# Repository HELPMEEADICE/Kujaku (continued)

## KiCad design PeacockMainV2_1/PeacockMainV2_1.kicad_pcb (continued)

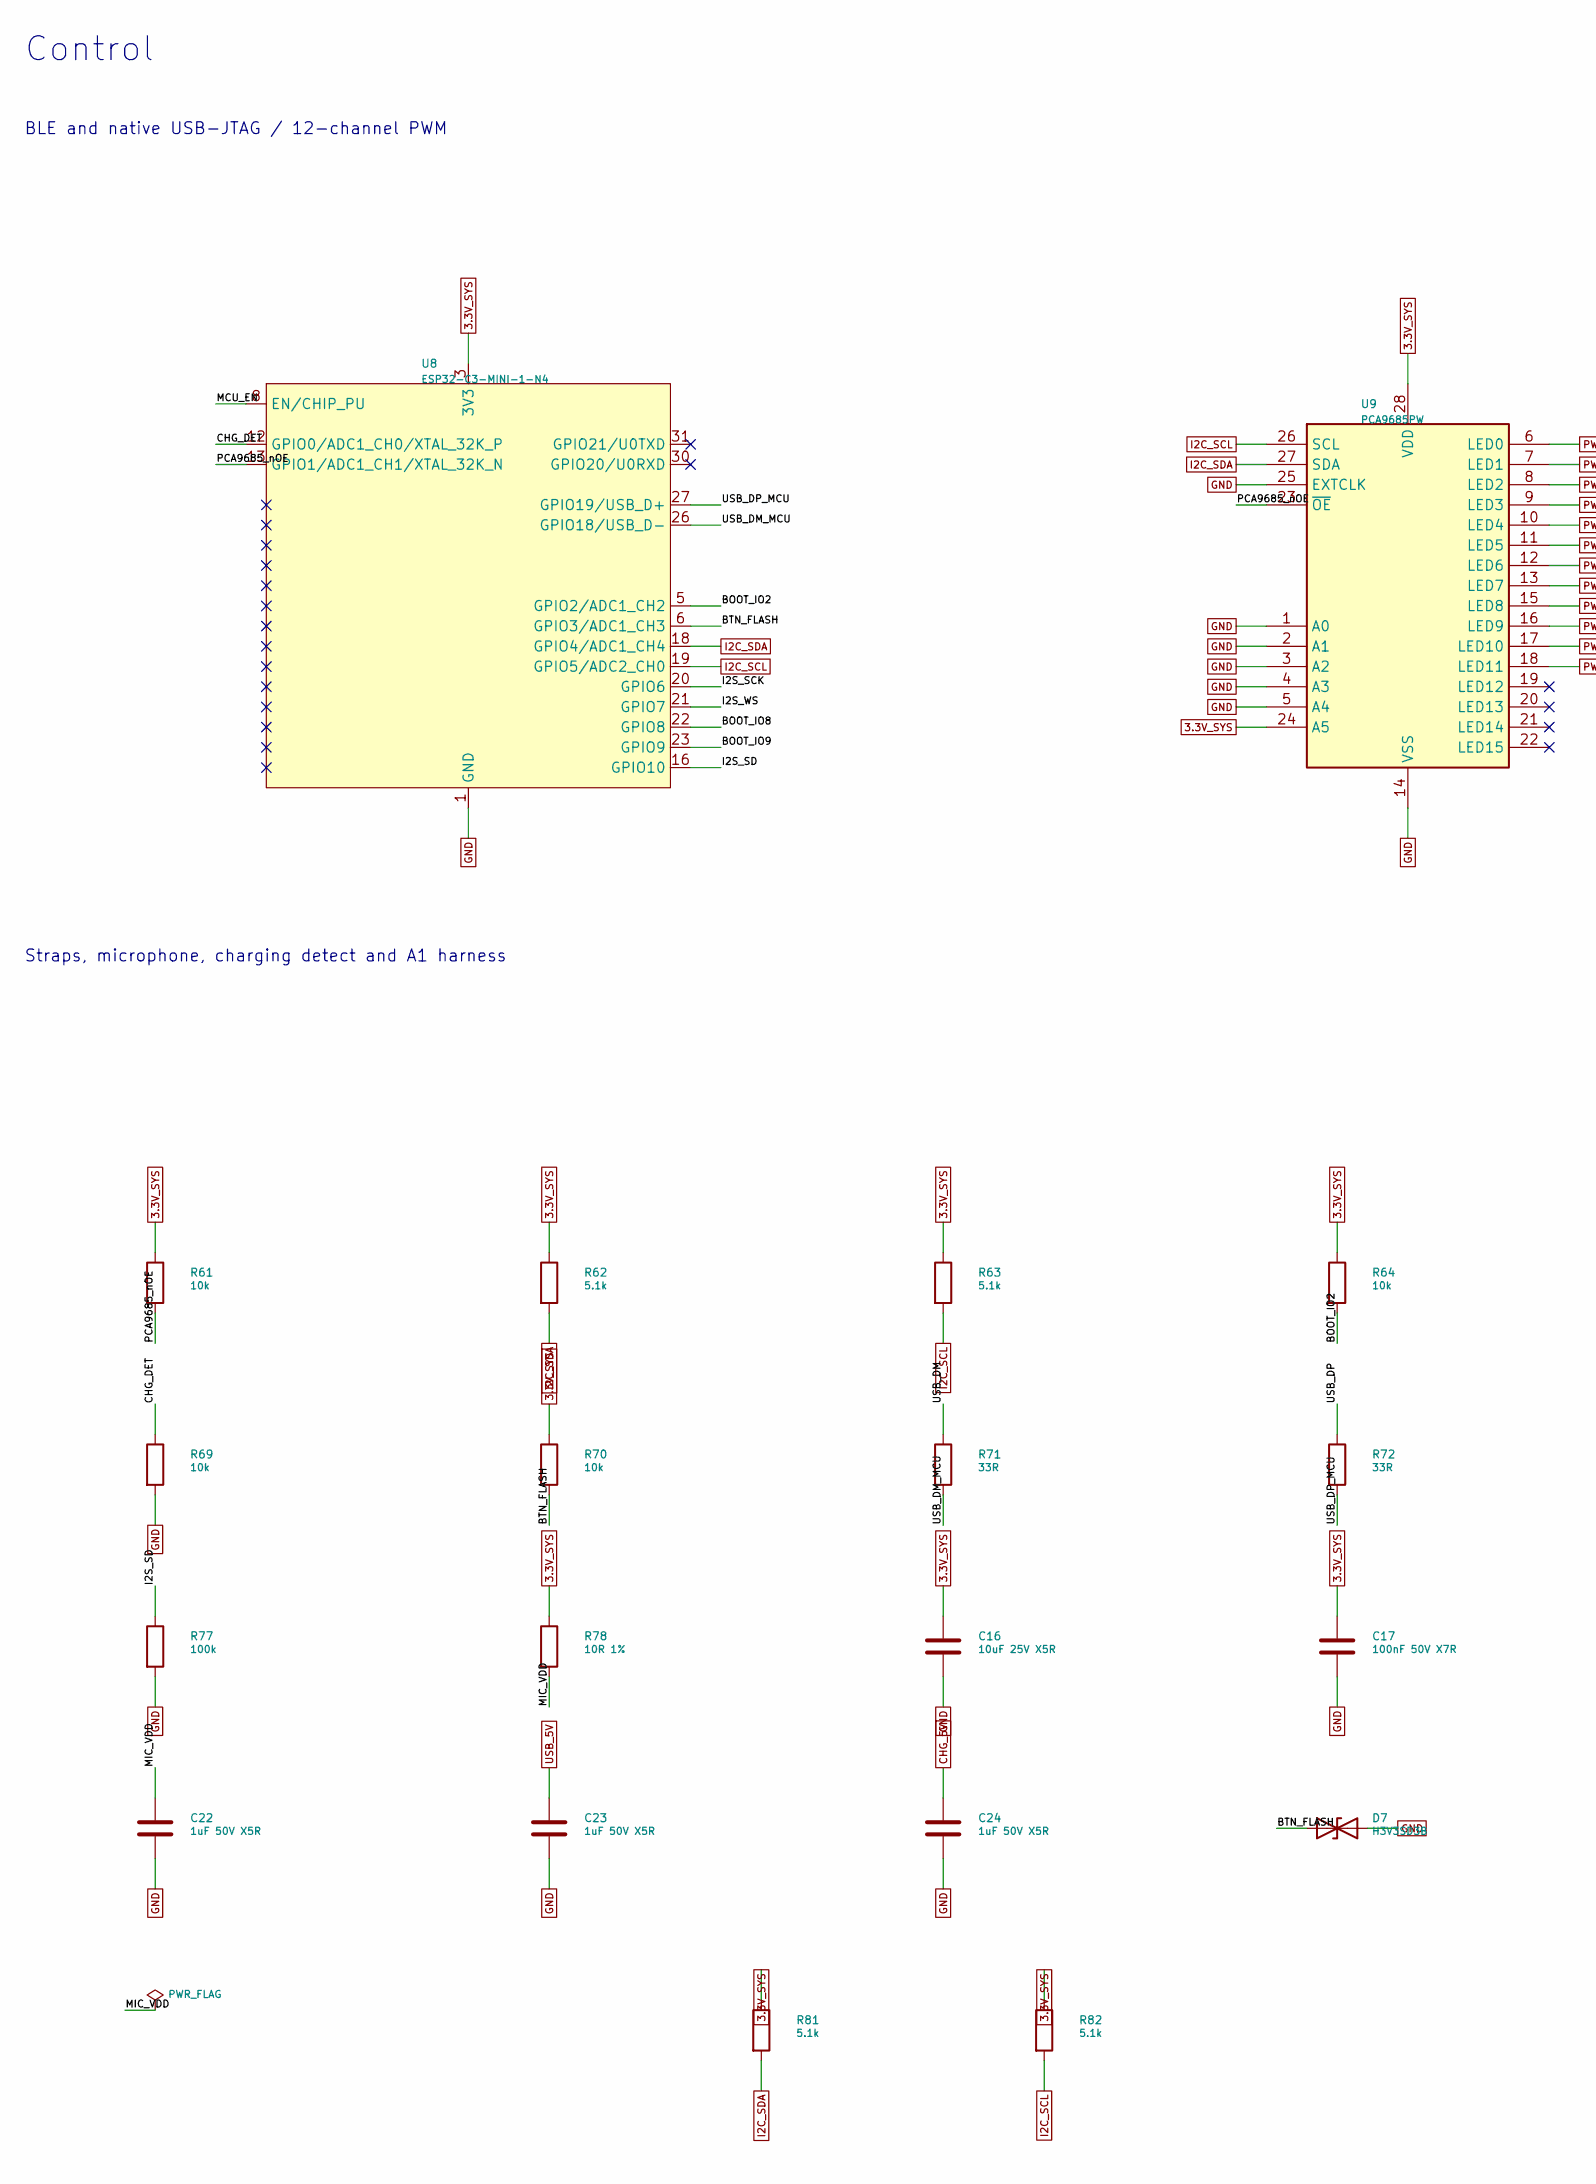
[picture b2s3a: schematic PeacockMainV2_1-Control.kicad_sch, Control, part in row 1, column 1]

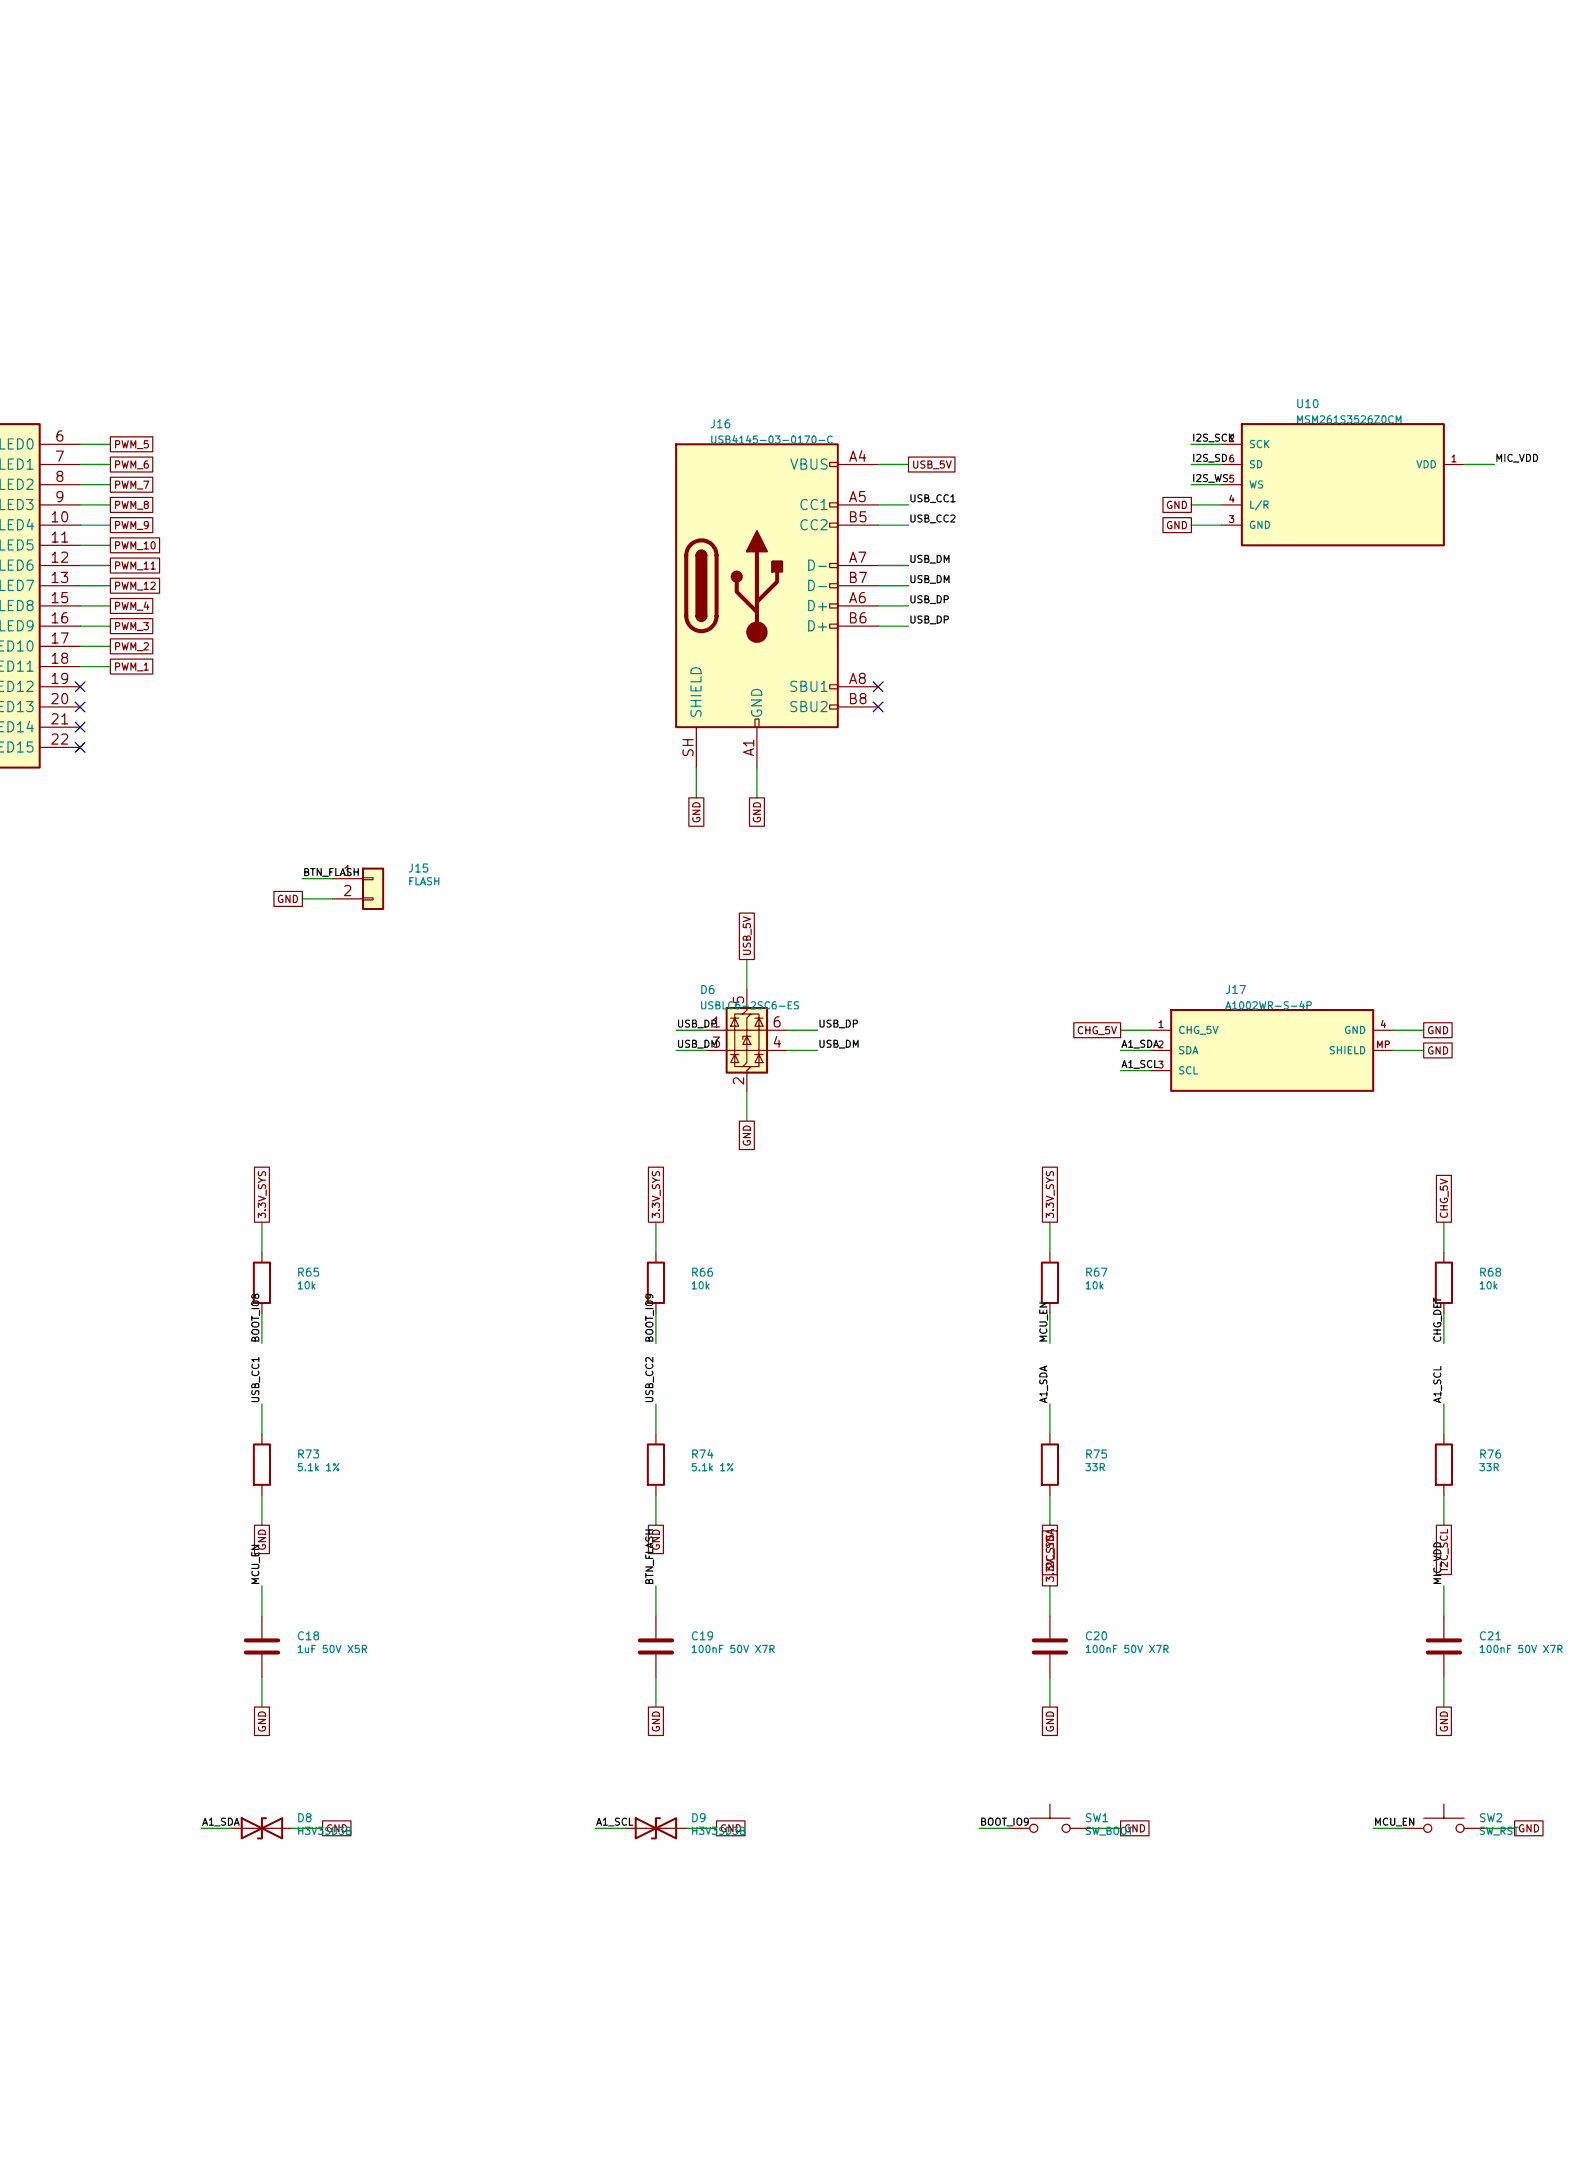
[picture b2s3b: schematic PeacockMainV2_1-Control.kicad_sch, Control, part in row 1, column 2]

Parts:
C16: 10uF 25V X5R; C_0805_2012Metric; MPN CL21A106KAYNNNE; LCSC C15850
C17, C21: 100nF 50V X7R; C_0402_1005Metric; MPN CL05B104KB54PNC; LCSC C307331
C18, C22, C23, C24: 1uF 50V X5R; C_0603_1608Metric; MPN CL10A105KB8NNNC; LCSC C15849
C19, C20: 100nF 50V X7R; C_0603_1608Metric; MPN CC0603KRX7R9BB104; LCSC C14663
D6: USBLC6-2SC6-ES; SOT-23-6; MPN USBLC6-2SC6-ES; LCSC C5180249
D7, D8, D9: H3V3SD3B; D_SOD-323; MPN H3V3SD3B; LCSC C20615802
J15: FLASH; Remote_Switch
J16: USB4145-03-0170-C; USB_C_Receptacle_GCT_USB4145-03-0170-C_Vertical; MPN USB4145-03-0170-C; LCSC C5181332
J17: A1002WR-S-4P; JST_SH_SM04B-SRSS-TB_1x04-1MP_P1.00mm_Horizontal; MPN A1002WR-S-4P; LCSC C239522
R61, R64, R65, R66, R67, R68, R69, R70: 10k; R_0603_1608Metric; MPN 0603WAF1002T5E; LCSC C25804
R62, R63, R81, R82: 5.1k; R_0603_1608Metric; MPN 0603WAF5101T5E; LCSC C23186
R71: 33R; R_0402_1005Metric; MPN 0402WGF330JTCE; LCSC C25105
R72, R75, R76: 33R; R_0603_1608Metric; MPN 0603WAF330JT5E; LCSC C23140
R73, R74: 5.1k 1%; R_0603_1608Metric; MPN 0603WAF5101T5E; LCSC C23186
R77: 100k; R_0603_1608Metric; MPN 0603WAF1003T5E; LCSC C25803
R78: 10R 1%; R_0603_1608Metric; MPN 0603WAF100JT5E; LCSC C22859
SW1: SW_BOOT; SW_SPST_TL3342; MPN TS5216A 160gf; LCSC C2681484
SW2: SW_RST; SW_SPST_TL3342; MPN TS5216A 160gf; LCSC C2681484
U8: ESP32-C3-MINI-1-N4; ESP32-C3-MINI-1; MPN ESP32-C3-MINI-1-N4; LCSC C2838502
U9: PCA9685PW; TSSOP-28_4.4x9.7mm_P0.65mm; MPN PCA9685PW,118; LCSC C2678753
U10: MSM261S3526Z0CM; MSM261S3526Z0CM_3.50x2.65; MPN MSM261S3526Z0CM; LCSC C966933

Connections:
3.3V_SYS: C16.1, C17.1, C20.1, R61.1, R62.1, R63.1, R64.1, R65.1, R66.1, R67.1, R70.1, R78.1, R81.1, R82.1, U8.3 (3V3), U9.24 (A5), U9.28 (VDD); also elsewhere on the board
/Control/A1_SCL: D9.1 (A1), J17.3 (SCL), R76.1
/Control/A1_SDA: D8.1 (A1), J17.2 (SDA), R75.1
/Control/BOOT_IO2: R64.2, U8.5 (GPIO2/ADC1_CH2)
/Control/BOOT_IO8: R65.2, U8.22 (GPIO8)
/Control/BOOT_IO9: R66.2, SW1.1, U8.23 (GPIO9)
/Control/BTN_FLASH: C19.1, D7.1 (A1), J15.1, R70.2, U8.6 (GPIO3/ADC1_CH3)
/Control/CHG_DET: R68.2, R69.1, U8.12 (GPIO0/ADC1_CH0/XTAL_32K_P)
/Control/I2S_SCK: U8.20 (GPIO6), U10.2 (SCK)
/Control/I2S_SD: R77.1, U8.16 (GPIO10), U10.6 (SD)
/Control/I2S_WS: U8.21 (GPIO7), U10.5 (WS)
/Control/MCU_EN: C18.1, R67.2, SW2.1, U8.8 (EN/CHIP_PU)
/Control/MIC_VDD: C21.1, C22.1, R78.2, U10.1 (VDD)
/Control/PCA9685_nOE: R61.2, U8.13 (GPIO1/ADC1_CH1/XTAL_32K_N), U9.23 (~OE)
/Control/USB_CC1: J16.A5 (CC1), R73.1
/Control/USB_CC2: J16.B5 (CC2), R74.1
/Control/USB_DM: D6.3 (I/O2), D6.4 (I/O2), J16.A7 (D-), J16.B7 (D-), R71.1
/Control/USB_DM_MCU: R71.2, U8.26 (GPIO18/USB_D-)
/Control/USB_DP: D6.1 (I/O1), D6.6 (I/O1), J16.A6 (D+), J16.B6 (D+), R72.1
/Control/USB_DP_MCU: R72.2, U8.27 (GPIO19/USB_D+)
CHG_5V: C24.1, J17.1 (CHG_5V), R68.1; also elsewhere on the board
GND: C16.2, C17.2, C18.2, C19.2, C20.2, C21.2, C22.2, C23.2, C24.2, D6.2 (GND), D7.2 (A2), D8.2 (A2), D9.2 (A2), J15.2, J16.A1 (GND), J16.A12 (GND), J16.B1 (GND), J16.B12 (GND), J16.SH (SHIELD), J17.4 (GND), J17.MP (SHIELD), R69.2, R73.2, R74.2, R77.2, SW1.2, SW2.2, U8.1 (GND), U8.2 (GND), U8.11 (GND), U8.14 (GND), U8.36 (GND), U8.37 (GND), U8.38 (GND), U8.39 (GND), U8.40 (GND), U8.41 (GND), U8.42 (GND), U8.43 (GND), U8.44 (GND), U8.45 (GND), U8.46 (GND), U8.47 (GND), U8.48 (GND), U8.49 (GND), U8.50 (GND), U8.51 (GND), U8.52 (GND), U8.53 (GND), U9.1 (A0), U9.2 (A1), U9.3 (A2), U9.4 (A3), U9.5 (A4), U9.14 (VSS), U9.25 (EXTCLK), U10.3 (GND), U10.4 (L/R); also elsewhere on the board
I2C_SCL: R63.2, R76.2, R82.2, U8.19 (GPIO5/ADC2_CH0), U9.26 (SCL); also elsewhere on the board
I2C_SDA: R62.2, R75.2, R81.2, U8.18 (GPIO4/ADC1_CH4), U9.27 (SDA); also elsewhere on the board
PWM_1: U9.18 (LED11); also elsewhere on the board
PWM_2: U9.17 (LED10); also elsewhere on the board
PWM_3: U9.16 (LED9); also elsewhere on the board
PWM_4: U9.15 (LED8); also elsewhere on the board
PWM_5: U9.6 (LED0); also elsewhere on the board
PWM_6: U9.7 (LED1); also elsewhere on the board
PWM_7: U9.8 (LED2); also elsewhere on the board
PWM_8: U9.9 (LED3); also elsewhere on the board
PWM_9: U9.10 (LED4); also elsewhere on the board
PWM_10: U9.11 (LED5); also elsewhere on the board
PWM_11: U9.12 (LED6); also elsewhere on the board
PWM_12: U9.13 (LED7); also elsewhere on the board
USB_5V: C23.1, D6.5 (VBUS), J16.A4 (VBUS), J16.A9 (VBUS), J16.B4 (VBUS), J16.B9 (VBUS); also elsewhere on the board

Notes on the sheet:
Control
BLE and native USB-JTAG / 12-channel PWM
Straps, microphone, charging detect and A1 harness

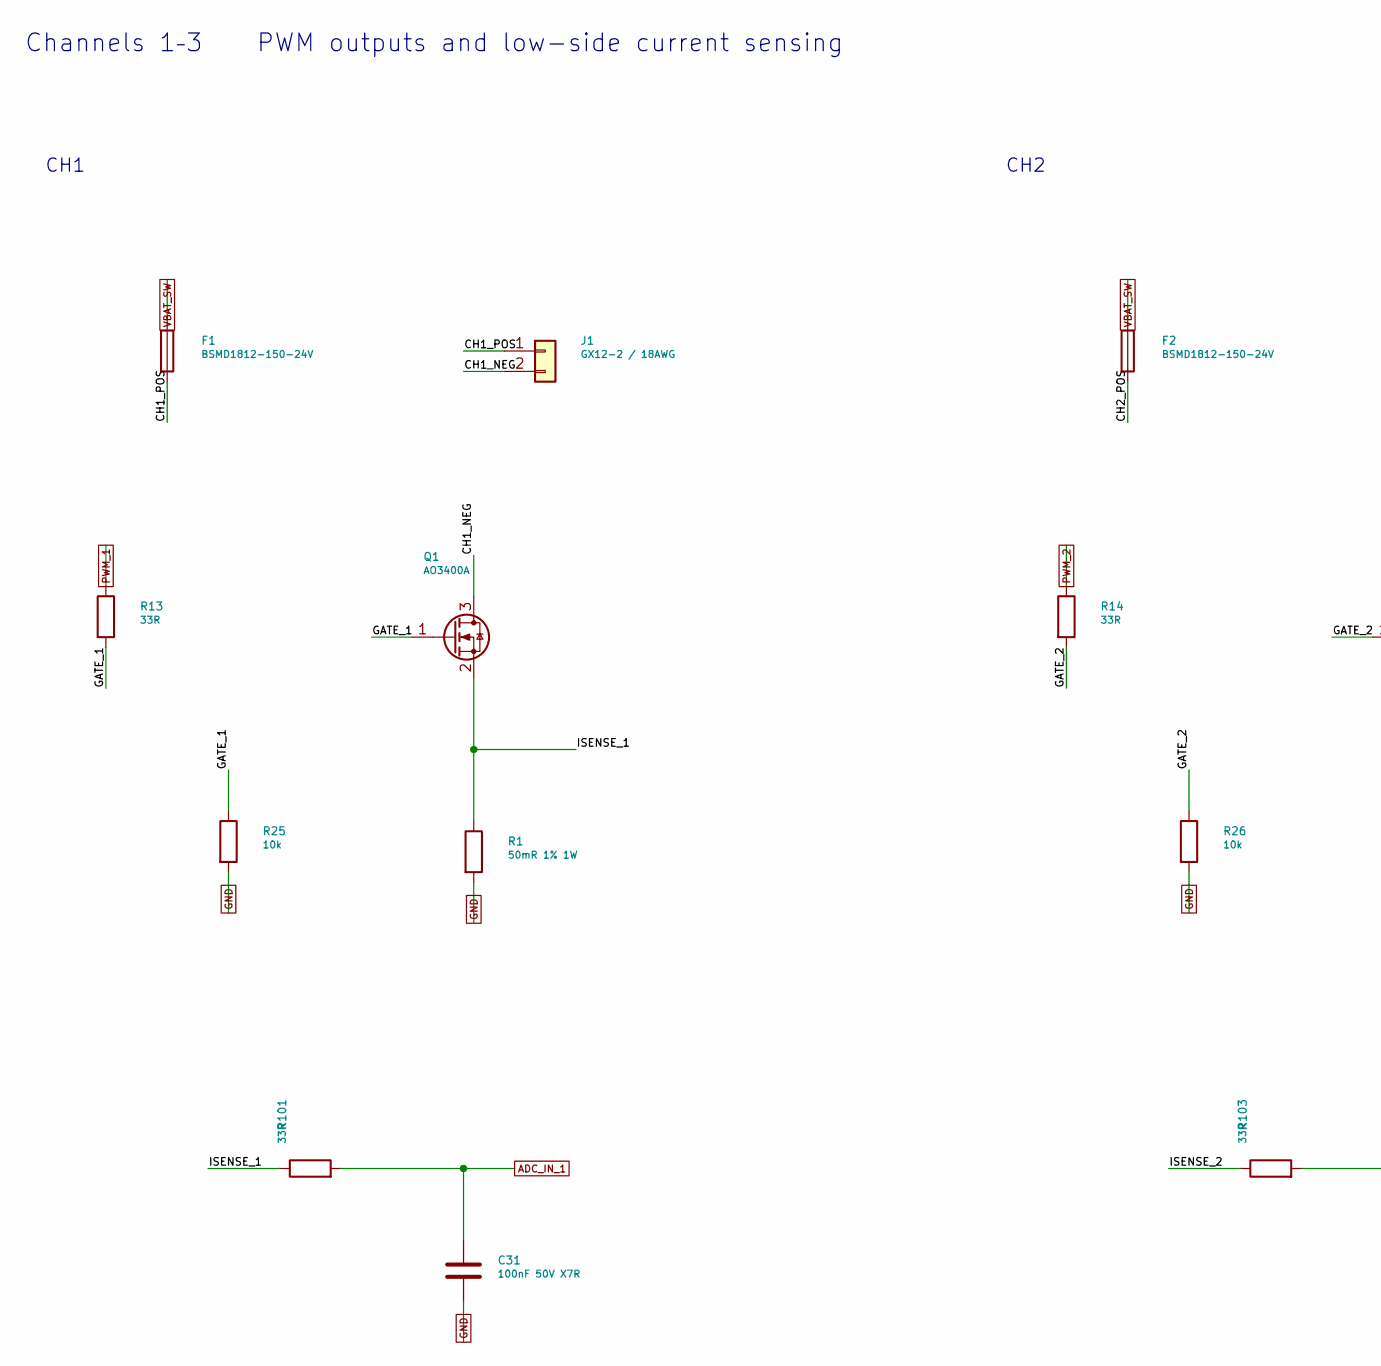
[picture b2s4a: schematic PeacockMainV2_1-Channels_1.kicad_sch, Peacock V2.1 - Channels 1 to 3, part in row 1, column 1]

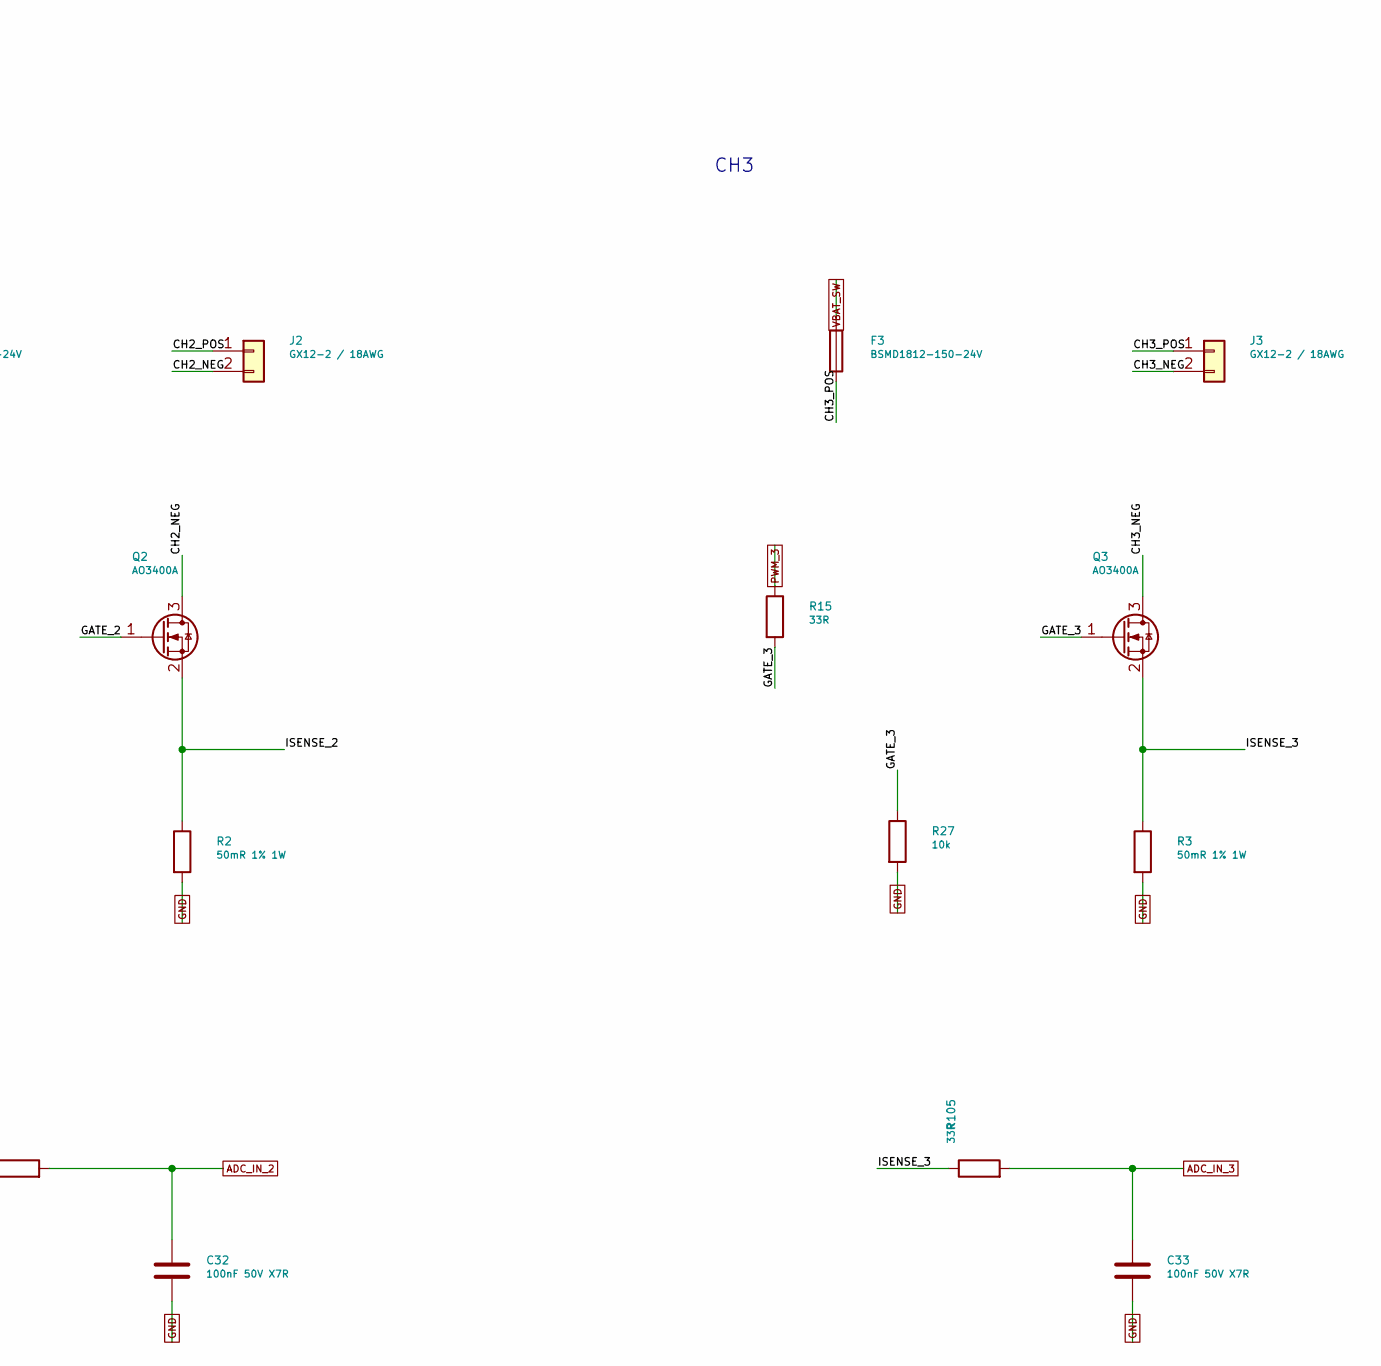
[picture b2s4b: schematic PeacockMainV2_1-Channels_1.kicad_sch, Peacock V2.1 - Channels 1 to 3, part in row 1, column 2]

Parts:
C31, C32, C33: 100nF 50V X7R; C_0603_1608Metric; MPN CC0603KRX7R9BB104; LCSC C14663
F1, F2, F3: BSMD1812-150-24V; R_1812_4532Metric; MPN BSMD1812-150-24V; LCSC C883153
J1, J2, J3: GX12-2 / 18AWG; GX12_Leadout_1x02_P5.00mm
Q1, Q2, Q3: AO3400A; SOT-23; MPN AO3400A; LCSC C20917
R1, R2, R3: 50mR 1% 1W; R_1206_3216Metric; MPN FRM121WFR050TM; LCSC C7467249
R13, R14, R15, R101, R103, R105: 33R; R_0603_1608Metric; MPN 0603WAF330JT5E; LCSC C23140
R25, R26, R27: 10k; R_0603_1608Metric; MPN 0603WAF1002T5E; LCSC C25804

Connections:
/Channels 1/CH1_NEG: J1.2, Q1.3 (D)
/Channels 1/CH1_POS: F1.2, J1.1
/Channels 1/CH2_NEG: J2.2, Q2.3 (D)
/Channels 1/CH2_POS: F2.2, J2.1
/Channels 1/CH3_NEG: J3.2, Q3.3 (D)
/Channels 1/CH3_POS: F3.2, J3.1
/Channels 1/GATE_1: Q1.1 (G), R13.2, R25.1
/Channels 1/GATE_2: Q2.1 (G), R14.2, R26.1
/Channels 1/GATE_3: Q3.1 (G), R15.2, R27.1
/Channels 1/ISENSE_1: Q1.2 (S), R1.1, R101.1
/Channels 1/ISENSE_2: Q2.2 (S), R2.1, R103.1
/Channels 1/ISENSE_3: Q3.2 (S), R3.1, R105.1
ADC_IN_1: C31.1, R101.2; also elsewhere on the board
ADC_IN_2: C32.1, R103.2; also elsewhere on the board
ADC_IN_3: C33.1, R105.2; also elsewhere on the board
GND: C31.2, C32.2, C33.2, R1.2, R2.2, R3.2, R25.2, R26.2, R27.2; also elsewhere on the board
PWM_1: R13.1; also elsewhere on the board
PWM_2: R14.1; also elsewhere on the board
PWM_3: R15.1; also elsewhere on the board
VBAT_SW: F1.1, F2.1, F3.1; also elsewhere on the board

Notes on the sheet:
Channels 1–3 PWM outputs and low-side current sensing
CH1
CH2
CH3

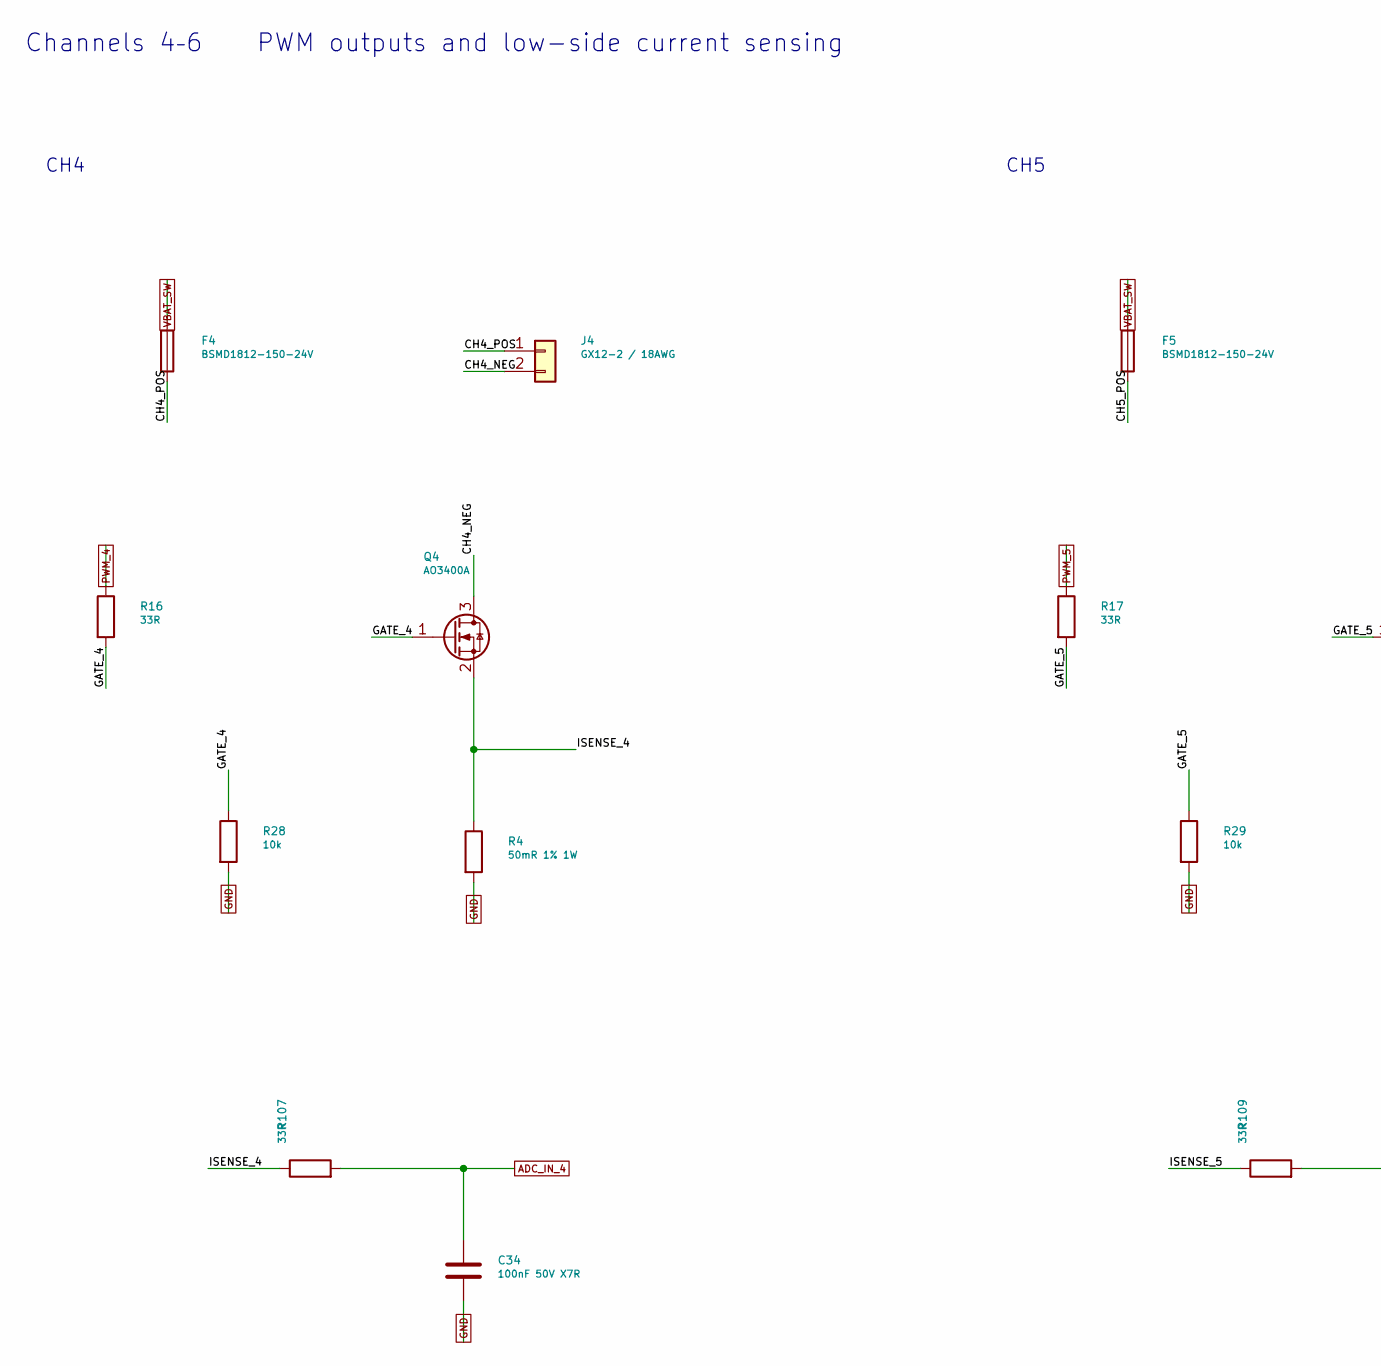
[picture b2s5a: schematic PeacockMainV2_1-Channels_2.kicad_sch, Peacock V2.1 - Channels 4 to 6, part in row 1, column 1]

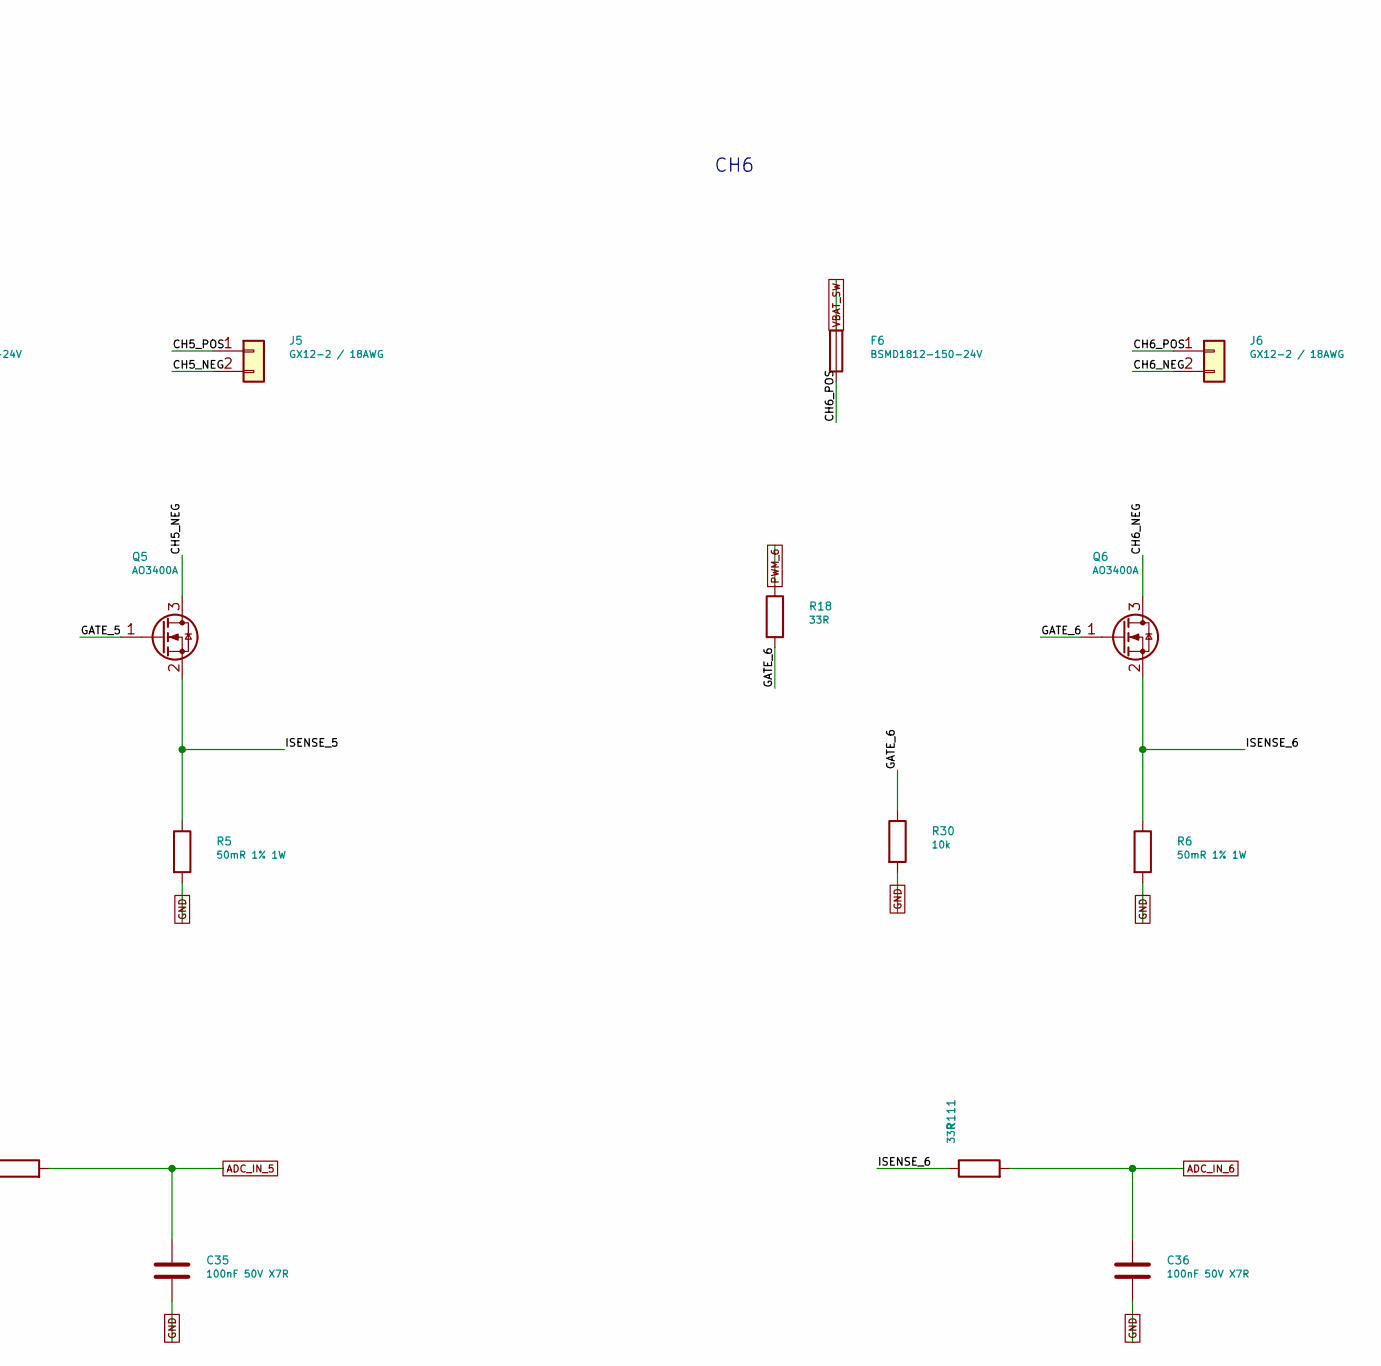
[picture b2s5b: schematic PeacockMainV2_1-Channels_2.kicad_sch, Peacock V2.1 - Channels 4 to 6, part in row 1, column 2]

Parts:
C34, C35, C36: 100nF 50V X7R; C_0603_1608Metric; MPN CC0603KRX7R9BB104; LCSC C14663
F4, F5, F6: BSMD1812-150-24V; R_1812_4532Metric; MPN BSMD1812-150-24V; LCSC C883153
J4, J5, J6: GX12-2 / 18AWG; GX12_Leadout_1x02_P5.00mm
Q4, Q5, Q6: AO3400A; SOT-23; MPN AO3400A; LCSC C20917
R4, R5, R6: 50mR 1% 1W; R_1206_3216Metric; MPN FRM121WFR050TM; LCSC C7467249
R16, R17, R18, R107, R109, R111: 33R; R_0603_1608Metric; MPN 0603WAF330JT5E; LCSC C23140
R28, R29, R30: 10k; R_0603_1608Metric; MPN 0603WAF1002T5E; LCSC C25804

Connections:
/Channels 2/CH4_NEG: J4.2, Q4.3 (D)
/Channels 2/CH4_POS: F4.2, J4.1
/Channels 2/CH5_NEG: J5.2, Q5.3 (D)
/Channels 2/CH5_POS: F5.2, J5.1
/Channels 2/CH6_NEG: J6.2, Q6.3 (D)
/Channels 2/CH6_POS: F6.2, J6.1
/Channels 2/GATE_4: Q4.1 (G), R16.2, R28.1
/Channels 2/GATE_5: Q5.1 (G), R17.2, R29.1
/Channels 2/GATE_6: Q6.1 (G), R18.2, R30.1
/Channels 2/ISENSE_4: Q4.2 (S), R4.1, R107.1
/Channels 2/ISENSE_5: Q5.2 (S), R5.1, R109.1
/Channels 2/ISENSE_6: Q6.2 (S), R6.1, R111.1
ADC_IN_4: C34.1, R107.2; also elsewhere on the board
ADC_IN_5: C35.1, R109.2; also elsewhere on the board
ADC_IN_6: C36.1, R111.2; also elsewhere on the board
GND: C34.2, C35.2, C36.2, R4.2, R5.2, R6.2, R28.2, R29.2, R30.2; also elsewhere on the board
PWM_4: R16.1; also elsewhere on the board
PWM_5: R17.1; also elsewhere on the board
PWM_6: R18.1; also elsewhere on the board
VBAT_SW: F4.1, F5.1, F6.1; also elsewhere on the board

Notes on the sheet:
Channels 4–6 PWM outputs and low-side current sensing
CH4
CH5
CH6
